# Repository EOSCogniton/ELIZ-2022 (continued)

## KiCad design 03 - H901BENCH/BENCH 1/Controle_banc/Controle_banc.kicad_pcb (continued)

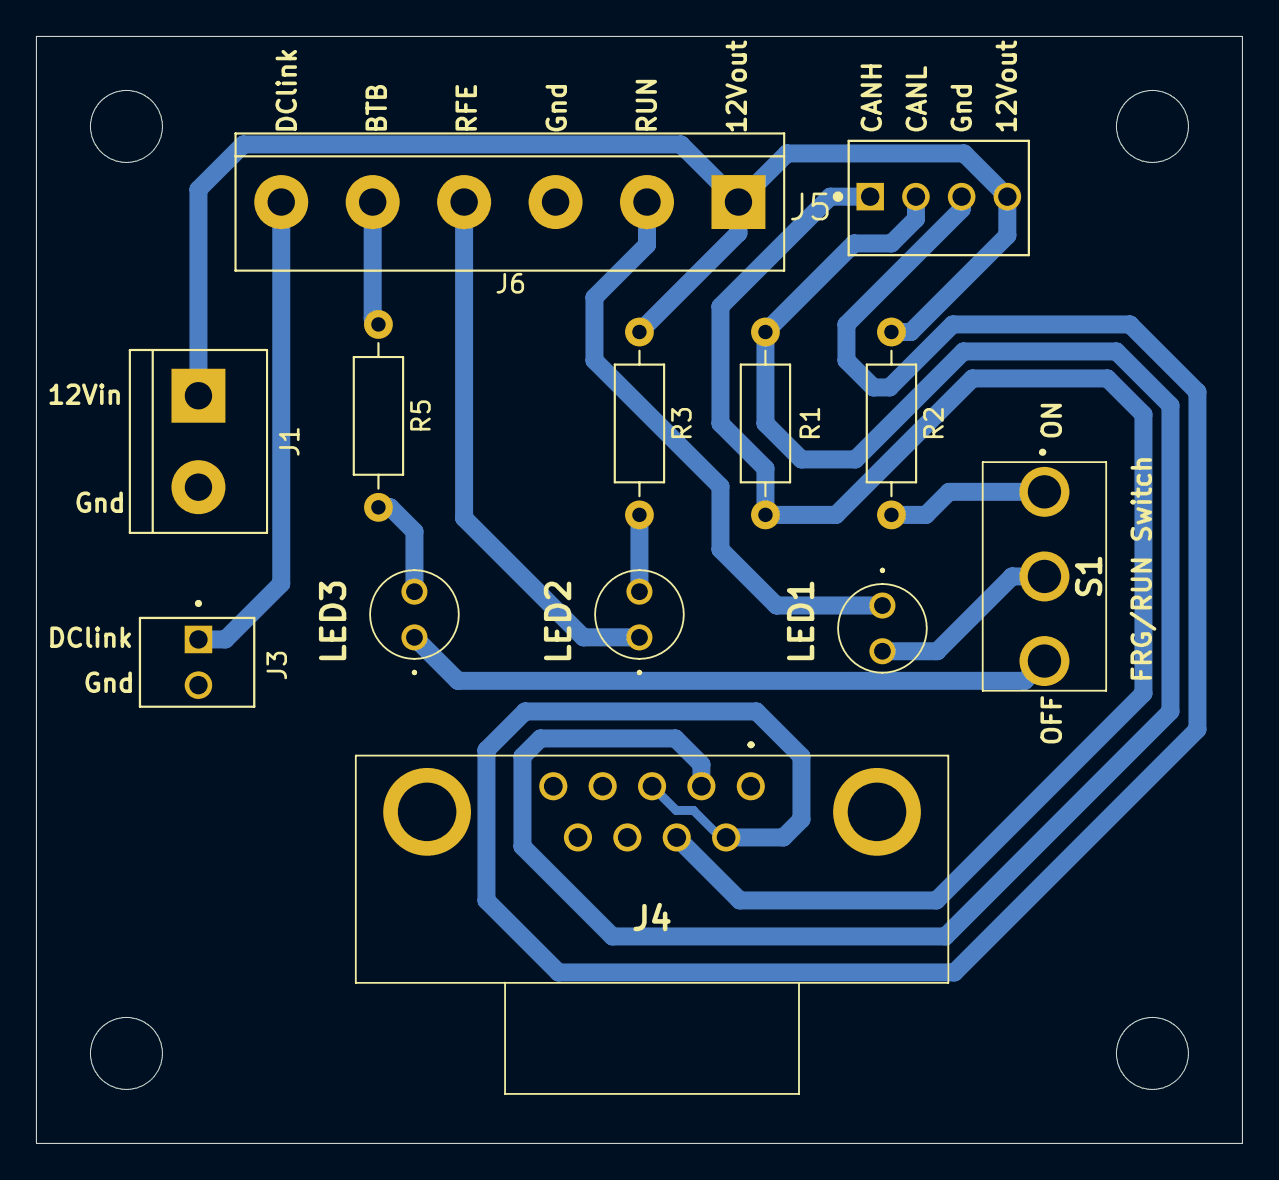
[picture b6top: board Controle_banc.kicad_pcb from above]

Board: 2 copper layers, 67.0 x 61.5 mm, 17 parts (0 on the bottom side), 13 nets.

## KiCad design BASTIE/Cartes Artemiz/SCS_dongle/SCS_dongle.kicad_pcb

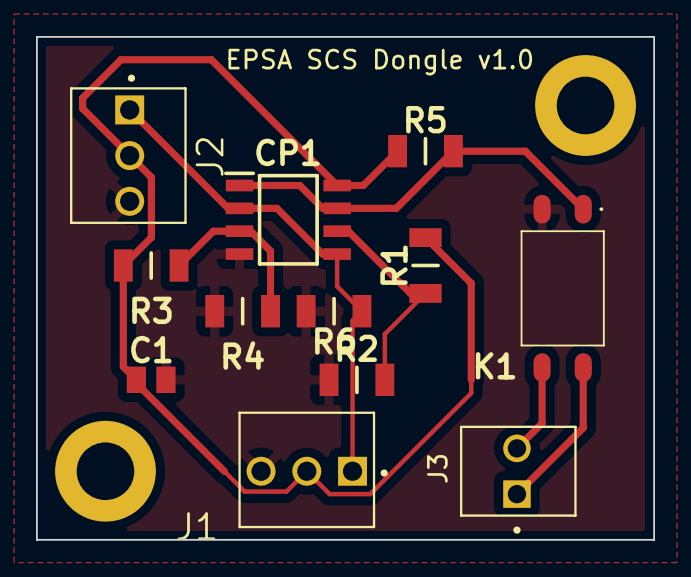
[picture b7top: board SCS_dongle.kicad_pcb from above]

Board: 2 copper layers, 34.3 x 27.9 mm, 12 parts (0 on the bottom side), 8 nets.

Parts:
C1: Condensateur 0805Y1000104JXT; CAPC2012X130N
CP1: Comparateur Double LM393LVDR; SOIC127P600X175-8N
J1, J2: 3P Droit 22-11-2032; MOLEX_22-11-2032
J3: 2P Droit 2-11-2022; MOLEX_22-11-2022
K1: SSR CPC1394GR; CPC1394GR
R1, R2, R3, R4, R5, R6: Résistance RK73H2BLTDD2152F; RESC3216X70N

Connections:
+5V: C1.1, CP1.8 (V+), J1.2, J2.2, R1.2, R3.2, R5.1
/1V: CP1.6 (IN2-), R1.1, R2.2
/4V: CP1.3 (IN1+), R3.1, R4.2
/HS IN: J3.1, K1.4 (LOAD_2)
/HS OUT: J3.2, K1.3 (LOAD_1)
/Opto In: CP1.1 (OUT1), CP1.7 (OUT2), K1.1 (+_CONTROL), R5.2
/Sensor Input: CP1.2 (IN1-), CP1.5 (IN2+), J1.1, J2.1, R6.1
GND: C1.2, CP1.4 (GND), J1.3, J2.3, K1.2 (-_CONTROL), R2.1, R4.1, R6.2
